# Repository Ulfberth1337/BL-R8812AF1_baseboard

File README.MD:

This is a baseboard for BL-R8812AF1 WI-FI Module.
USB and Power can be suplied by USB TYPE-C connector or by using TH Pads.
Power requirments are 5V +/- 5% and current 1A.
Baseboard got resetable fuse in order to protect power supply from short circuit and reverse polarity protection.

!!! USE AT OWN RISK !!!

UPD reverse polarity protection part will not work, I mixed up source with drain on mosfet.
The rest of the board works fine.

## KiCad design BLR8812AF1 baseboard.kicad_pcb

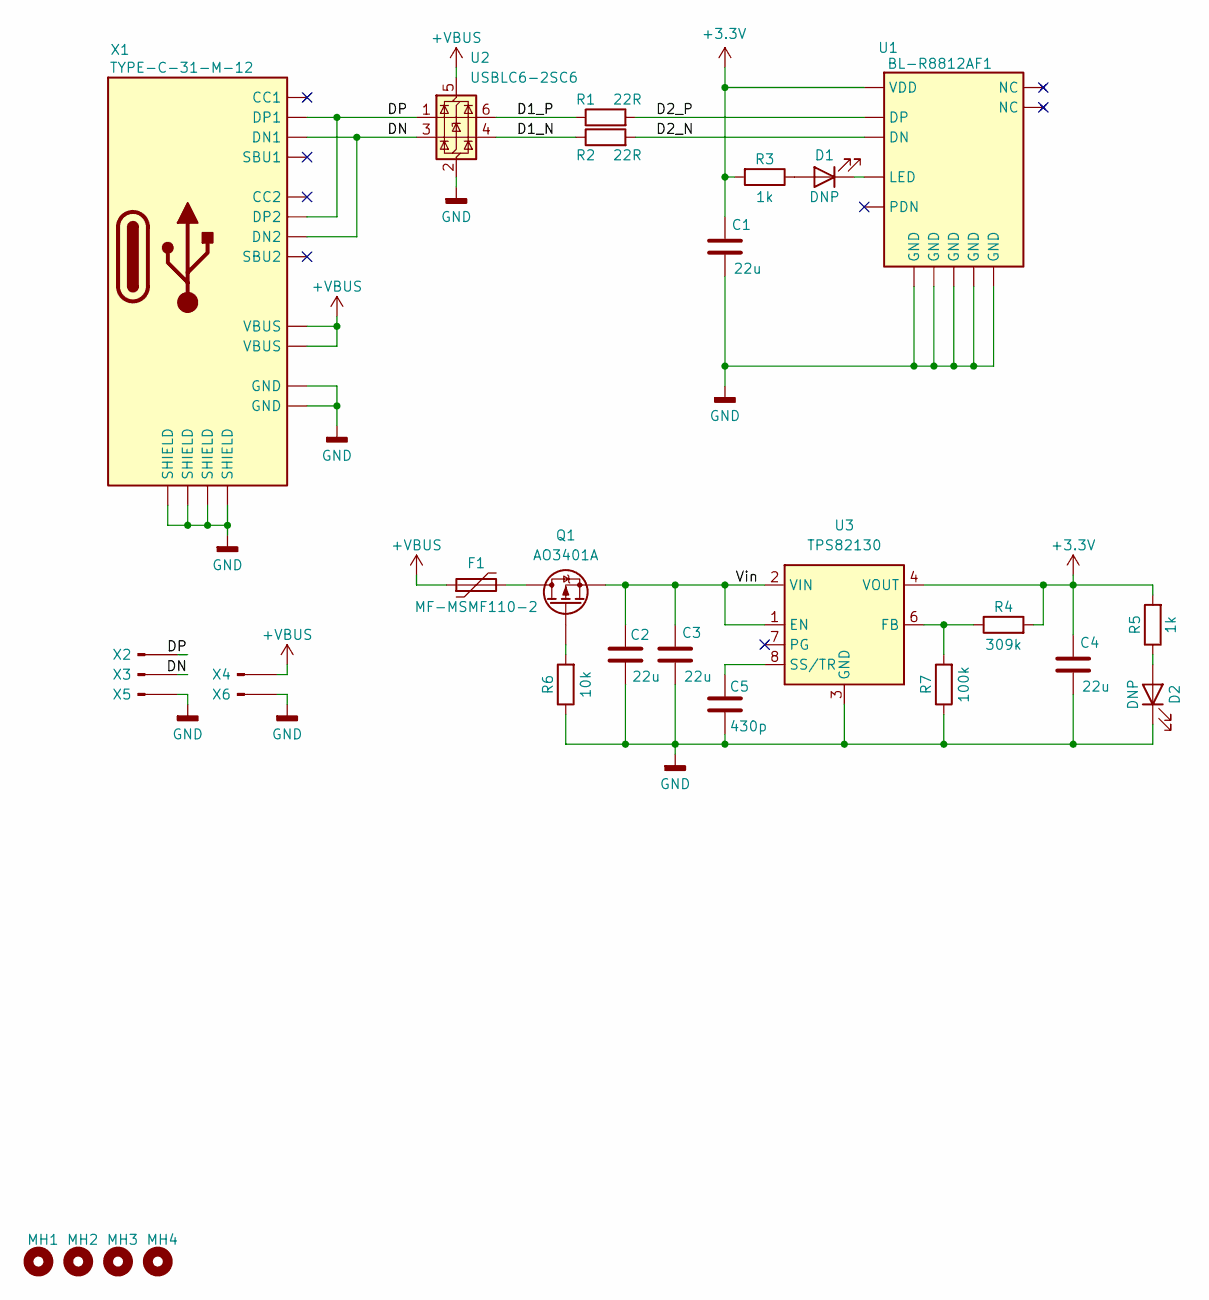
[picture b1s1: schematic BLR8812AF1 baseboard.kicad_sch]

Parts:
C1, C2, C3, C4: 22u; C_1206_3216Metric
C5: 430p; C_0402_1005Metric
D1, D2: DNP; LED_0603_1608Metric
F1: MF-MSMF110-2; Fuse_1812_4532Metric_Pad1.30x3.40mm_HandSolder
MH1, MH2, MH3, MH4: MountingHole; MountingHole_2.2mm_M2
Q1: AO3401A; SOT-23
R1, R2: 22R; R_0402_1005Metric
R3, R5: 1k; R_0402_1005Metric
R4: 309k; R_0402_1005Metric
R6: 10k; R_0402_1005Metric
R7: 100k; R_0402_1005Metric
U1: BL-R8812AF1
U2: USBLC6-2SC6; SOT-23-6
U3: TPS82130; Texas_SIL0008D_MicroSiP-8-1EP_2.8x3mm_P0.65mm_EP1.1x1.9mm
X1: TYPE-C-31-M-12; HRO-TYPE-C-31-M-12
X2, X3, X5: TH_1_1_0.65
X4, X6: TH_1.7_1.7_1

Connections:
+3.3V: C1.1, C4.1, R3.2, R4.2, R5.2, U1.2 (VDD), U3.4 (VOUT), U3.5 (VOUT)
+VBUS: F1.1, U2.5 (VBUS), X1.A4B9 (VBUS), X1.B4A9 (VBUS), X4.1
/D1_N: R2.1, U2.4 (I/O2)
/D1_P: R1.1, U2.6 (I/O1)
/D2_N: R2.2, U1.3 (DN)
/D2_P: R1.2, U1.4 (DP)
/DN: U2.3 (I/O2), X1.A7 (DN1), X1.B7 (DN2), X3.1
/DP: U2.1 (I/O1), X1.A6 (DP1), X1.B6 (DP2), X2.1
/Vin: C2.1, C3.1, Q1.2 (S), U3.1 (EN), U3.2 (VIN)
GND: C1.2, C2.2, C3.2, C4.2, C5.2, D2.1 (K), R6.1, R7.1, U1.5 (GND), U1.7 (GND), U1.9 (GND), U1.10 (GND), U1.12 (GND), U2.2 (GND), U3.3 (GND), U3.9 (GND), X1.A1B12 (GND), X1.B1A12 (GND), X1.SHIELD, X5.1, X6.1
unnamed: D1.2 (A), R3.1
unnamed: D1.1 (K), U1.6 (LED)
unnamed: D2.2 (A), R5.1
unnamed: F1.2, Q1.3 (D)
unnamed: Q1.1 (G), R6.2
unnamed: R4.1, R7.2, U3.6 (FB)
unnamed: C5.1, U3.8 (SS/TR)

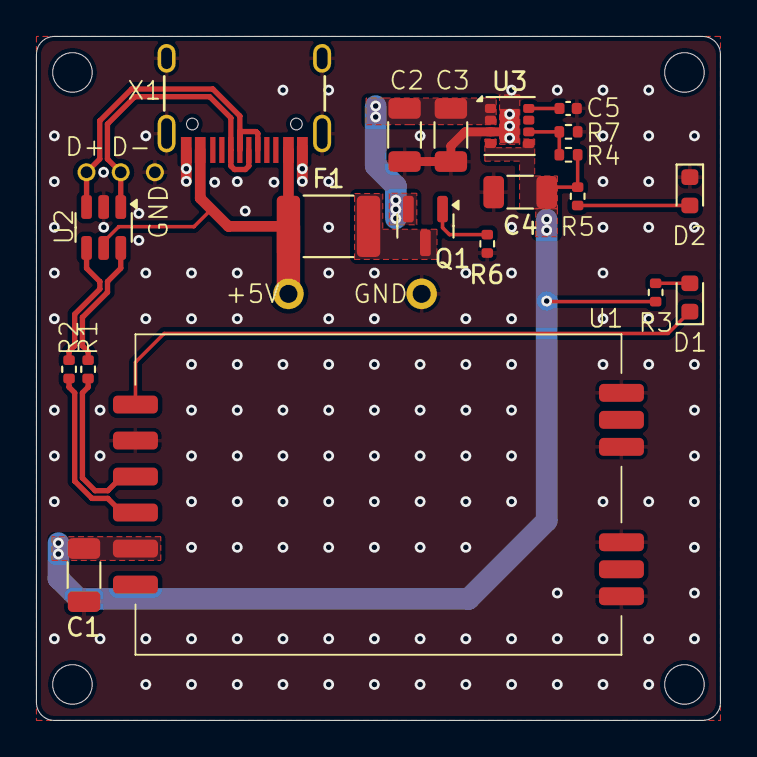
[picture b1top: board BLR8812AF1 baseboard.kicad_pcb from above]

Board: 2 copper layers, 38.0 x 38.0 mm, 29 parts (0 on the bottom side), 17 nets.

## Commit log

2024-10-19 Working on board
2024-10-26 Completed placing
2024-10-28 changed DC-DC
2024-11-09 almost done
2024-11-09 Done placing and routing, need to add stiching vias
2024-11-09 added README
2024-11-09 changed README
2024-11-09 PCB done
2024-11-09 DONE
2024-12-24 Fixed reverce voltage protection
2024-12-24 Fixed PCB and gerber files
